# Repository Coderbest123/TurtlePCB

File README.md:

# TurtlePCB
My PCB project that will be a turtle for half life
This PCB board is inspired by a turtle and the LED's are its flippers and eyes
It has lighting components and a timer so that the LED's can blink

Here is the image of the schematic:

Here is the image of the PCB:

Here is the image of the 3d view:

Here is my bill of materials:
| Part Name | Cost | Quantity | Vendor | Cart Image |
| :--- | :--- | :--- | :--- | :--- |
| Turtle PCB | $23.11 | 1 | JLCPCB |  |
| **Total** | **$23.11** | | | |

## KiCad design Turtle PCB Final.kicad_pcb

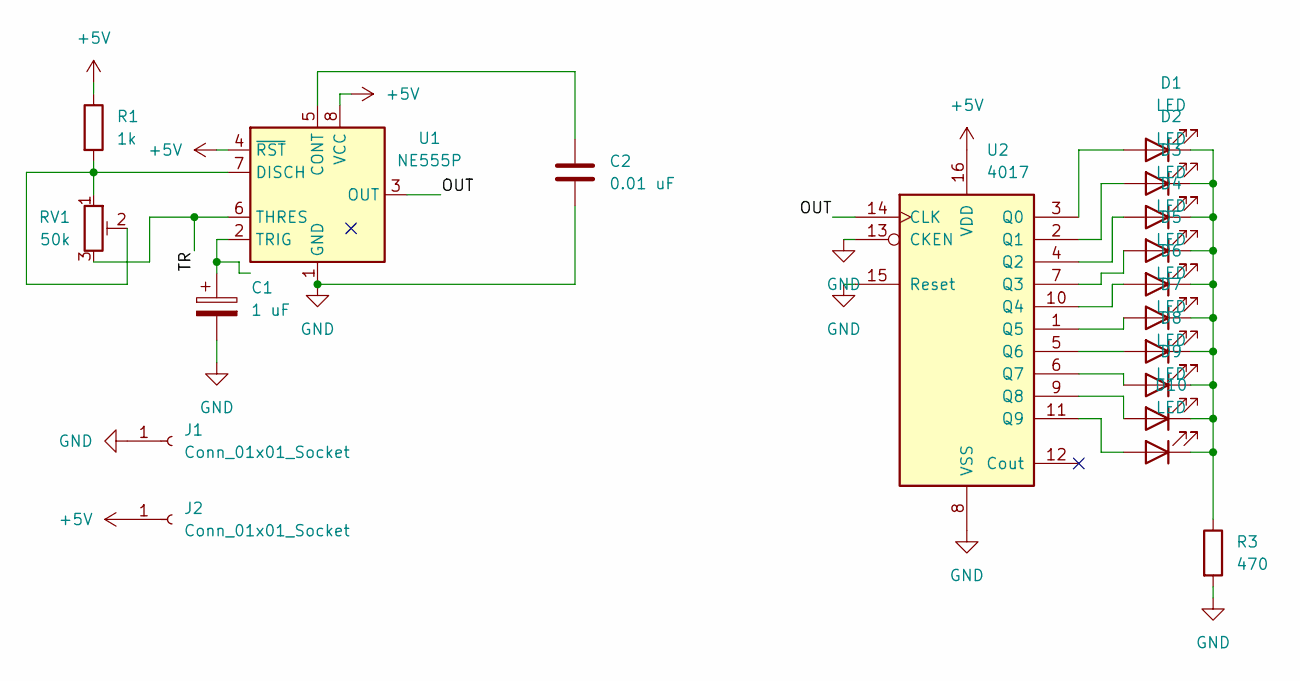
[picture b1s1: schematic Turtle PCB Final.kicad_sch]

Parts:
C1: 1 uF; CP_Radial_D5.0mm_P2.00mm
C2: 0.01 uF; C_Disc_D7.5mm_W2.5mm_P5.00mm
D1, D2, D3, D4, D5, D6, D7, D8, D9, D10: LED; LED_Cree-XHP50_3V_HighDensity
J1, J2: Conn_01x01_Socket; PinHeader_1x01_P2.54mm_Vertical
R1: 1k; R_Axial_DIN0207_L6.3mm_D2.5mm_P7.62mm_Horizontal
R3: 470; R_Axial_DIN0207_L6.3mm_D2.5mm_P7.62mm_Horizontal
RV1: 50k; R_Array_SIP8
U1: NE555P; DIP-8_W7.62mm
U2: 4017; PLCC-84_29.3x29.3mm_P1.27mm

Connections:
+5V: J2.1 (Pin_1_1), R1.1, U1.4 (~RST), U1.8 (VCC), U2.16 (VDD)
/OUT: U1.3 (OUT), U2.14 (CLK)
/TR: RV1.3, U1.6 (THRES)
GND: C1.2, C2.2, J1.1 (Pin_1_1), R3.2, U1.1 (GND), U2.8 (VSS), U2.13 (CKEN), U2.15 (Reset)
unnamed: D1.2 (A), U2.3 (Q0)
unnamed: D1.1 (K), D2.1 (K), D3.1 (K), D4.1 (K), D5.1 (K), D6.1 (K), D7.1 (K), D8.1 (K), D9.1 (K), D10.1 (K), R3.1
unnamed: D2.2 (A), U2.2 (Q1)
unnamed: D3.2 (A), U2.4 (Q2)
unnamed: D4.2 (A), U2.7 (Q3)
unnamed: D5.2 (A), U2.10 (Q4)
unnamed: D6.2 (A), U2.1 (Q5)
unnamed: D7.2 (A), U2.5 (Q6)
unnamed: D8.2 (A), U2.6 (Q7)
unnamed: D9.2 (A), U2.9 (Q8)
unnamed: D10.2 (A), U2.11 (Q9)
unnamed: C2.1, U1.5 (CONT)
unnamed: R1.2, RV1.1, RV1.2, U1.7 (DISCH)
unnamed: C1.1, U1.2 (TRIG)

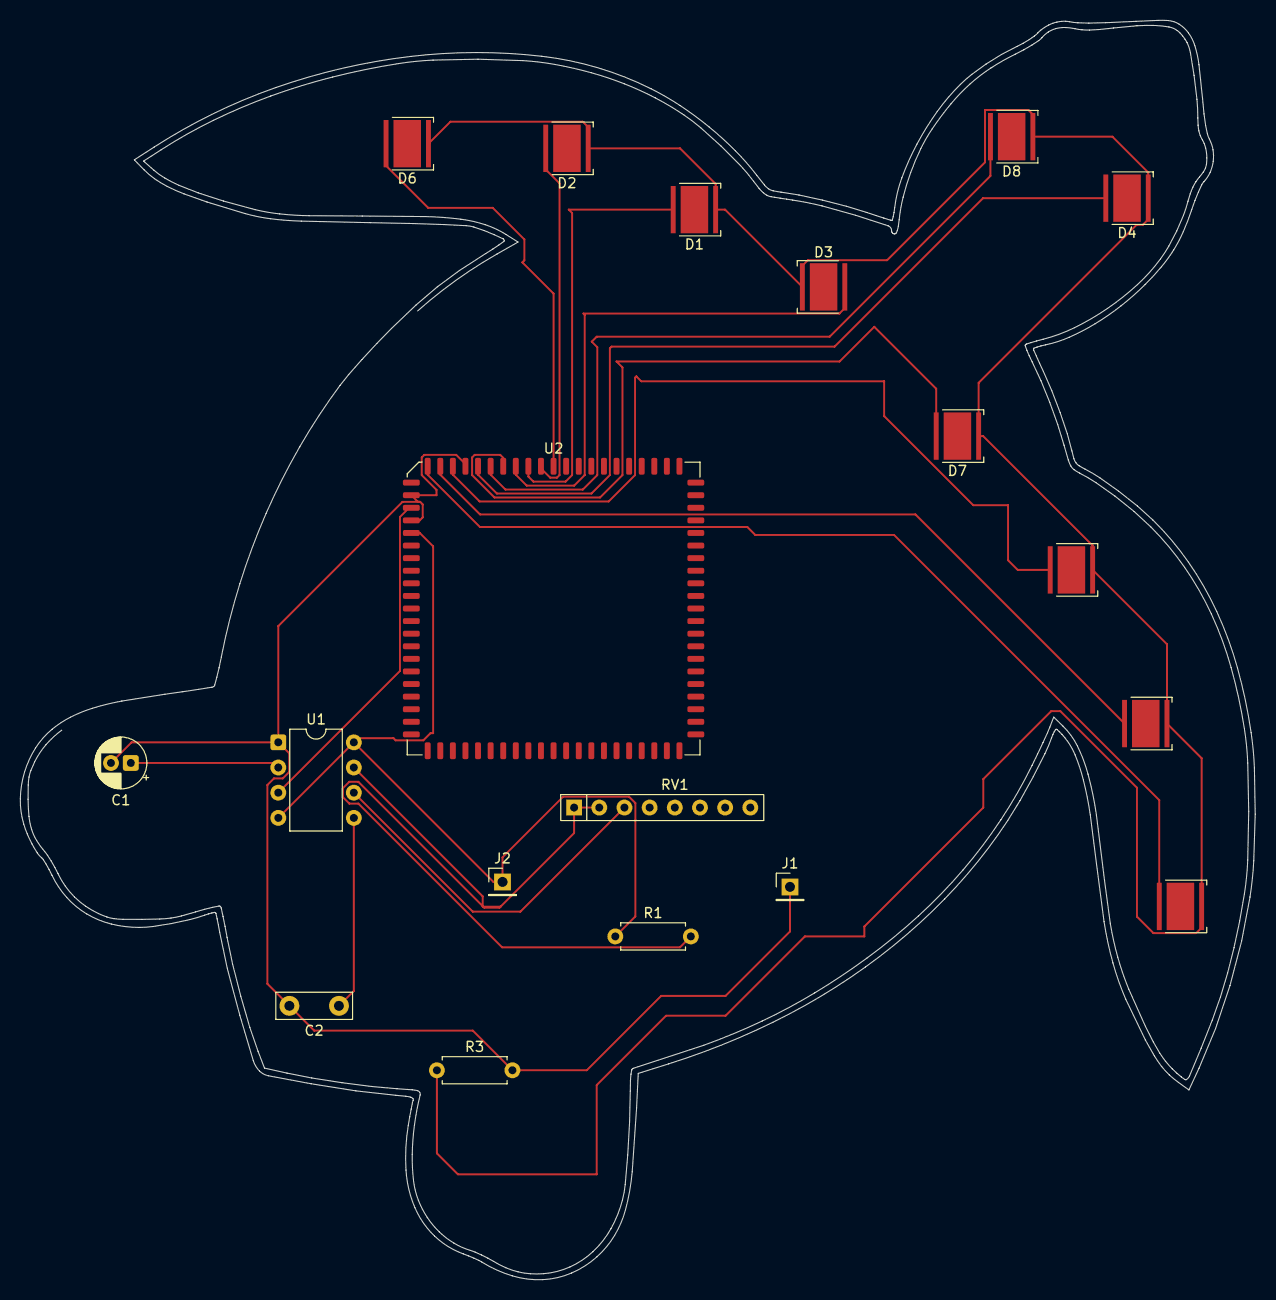
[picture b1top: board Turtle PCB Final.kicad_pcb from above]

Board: 2 copper layers, 124.6 x 127.0 mm, 19 parts (0 on the bottom side), 18 nets.
